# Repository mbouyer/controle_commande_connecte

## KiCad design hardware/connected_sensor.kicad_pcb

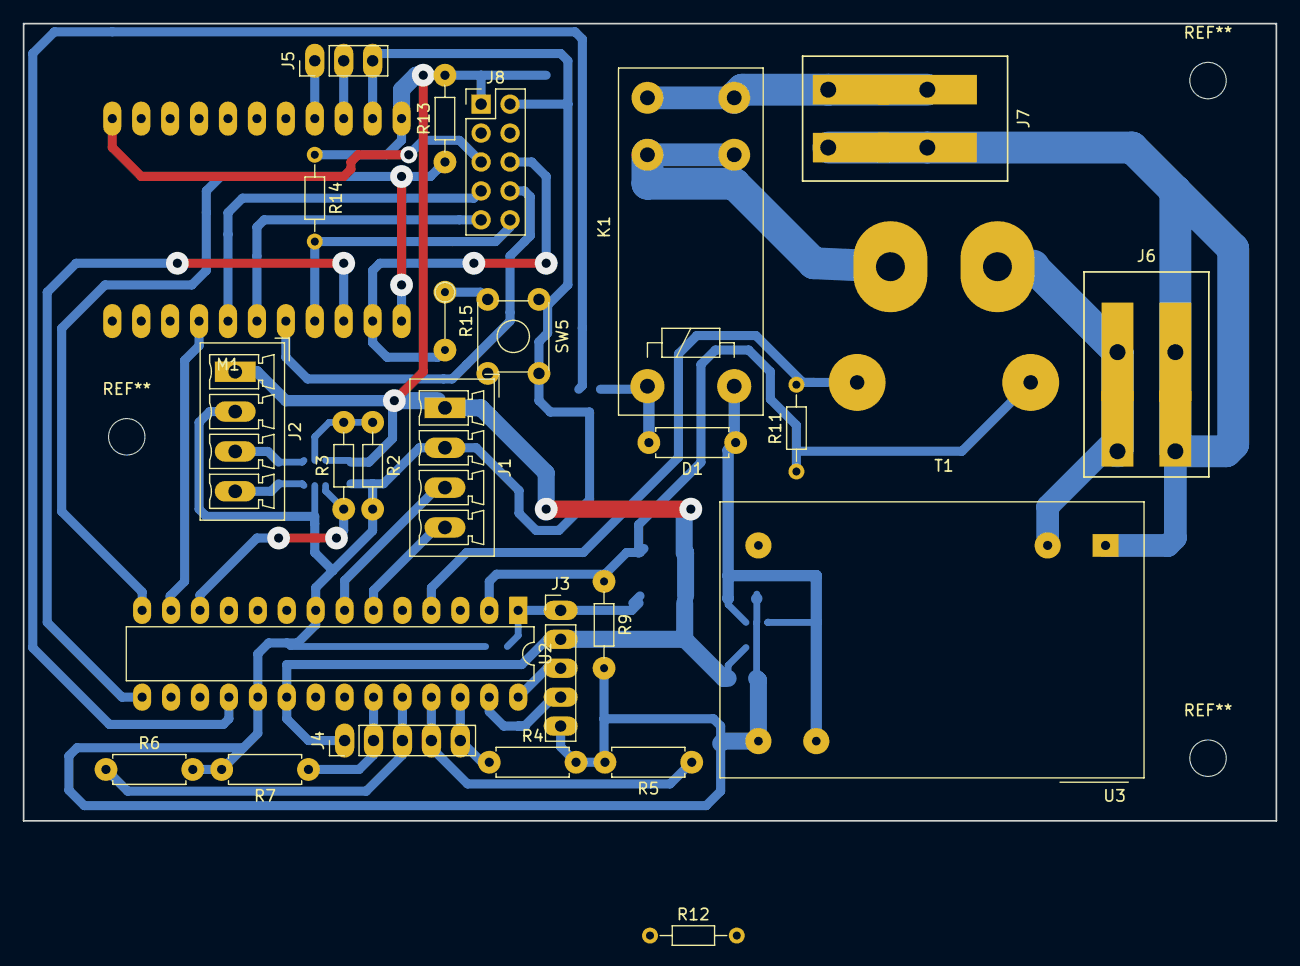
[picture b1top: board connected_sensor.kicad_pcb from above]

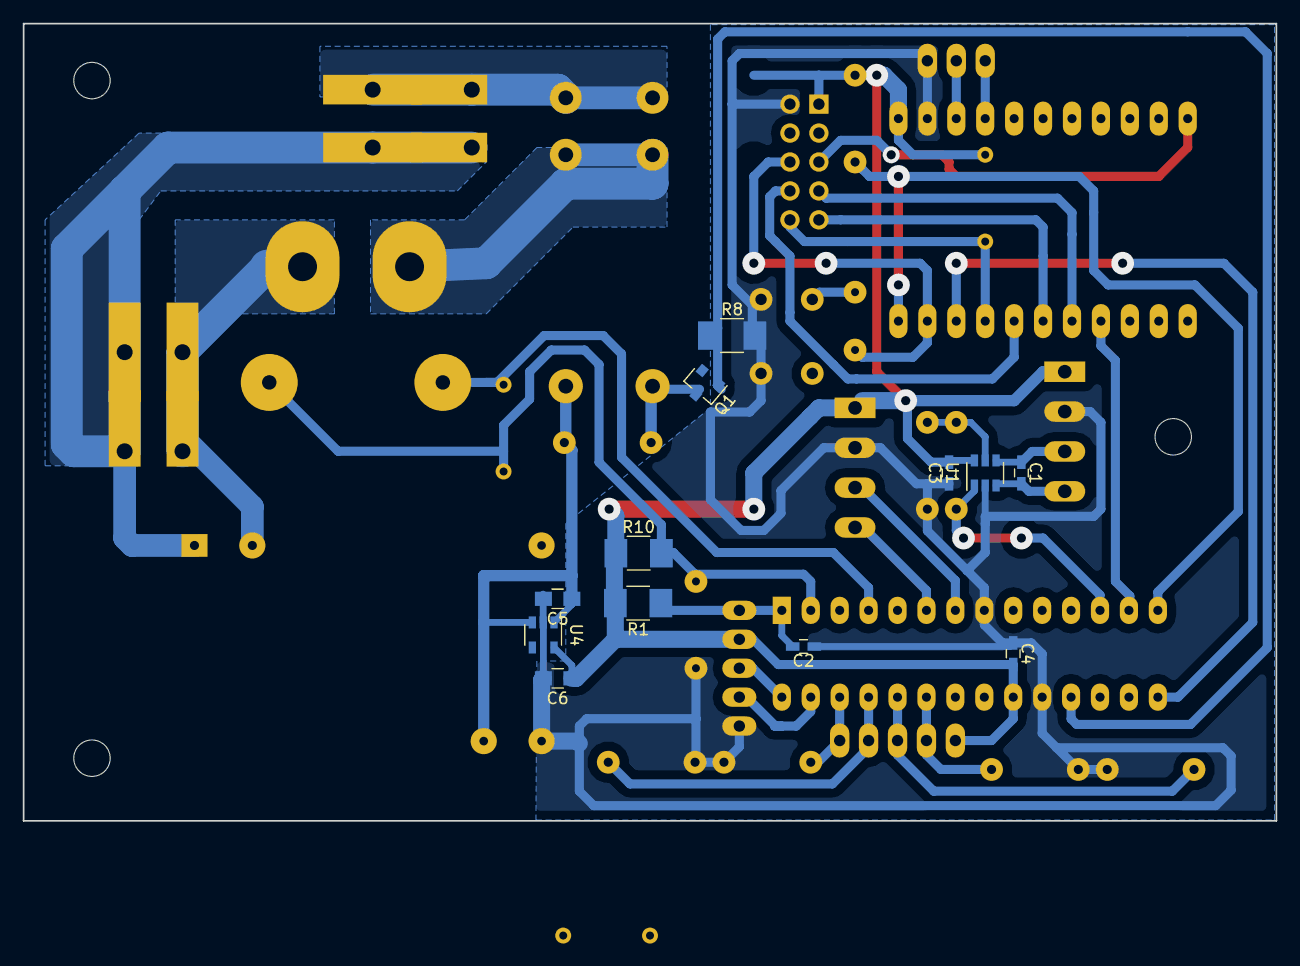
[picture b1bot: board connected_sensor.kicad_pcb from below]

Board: 2 copper layers, 110.0 x 70.0 mm, 39 parts (12 on the bottom side), 36 nets.

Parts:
C1, C2, C3, C4: 100nF; C_0603_HandSoldering
C5, C6: 1µ; C_0805_HandSoldering
D1: 1N4004; R_Axial_DIN0207_L6.3mm_D2.5mm_P7.62mm_Horizontal
J1, J2: Conn_01x04; PhoenixContact_MCV-G_04x3.50mm_Vertical
J3, J4: Conn_01x05; Pin_Header_Straight_1x05_Pitch2.54mm
J5: Conn_01x03; Pin_Header_Straight_1x03_Pitch2.54mm
J6: AC_IN; 1017491
J7: LOAD; 1017491
J8: UEXT; Pin_Header_Straight_2x05_Pitch2.54mm
K1: G2RL-1A-E 5DC; Relay_SPST_Schrack-RT1-16A-FormA_RM5mm
M1: ESP8266-DEV
Q1: ZXMN3A01FTA; SOT-23
R1, R8: 10K; R_1210_HandSoldering
R2: 5.6K; R_Axial_DIN0204_L3.6mm_D1.6mm_P7.62mm_Horizontal
R3: 100K; R_Axial_DIN0204_L3.6mm_D1.6mm_P7.62mm_Horizontal
R4, R5, R6, R7: 10K; R_Axial_DIN0207_L6.3mm_D2.5mm_P7.62mm_Horizontal
R9: 4.7k; R_Axial_DIN0204_L3.6mm_D1.6mm_P7.62mm_Horizontal
R10: 10k; R_1210_HandSoldering
R11: 18; R_Axial_DIN0204_L3.6mm_D1.6mm_P7.62mm_Horizontal
R12: NA; R_Axial_DIN0204_L3.6mm_D1.6mm_P7.62mm_Horizontal
R13: 2.2K; R_Axial_DIN0204_L3.6mm_D1.6mm_P7.62mm_Horizontal
R14: 47K; R_Axial_DIN0204_L3.6mm_D1.6mm_P7.62mm_Horizontal
R15: 220; R_Axial_DIN0204_L3.6mm_D1.6mm_P5.08mm_Vertical
SW5: SW_Push; SW_TH_Tactile_Omron_B3F-10xx
T1: Transformer_1P_1S; CSE187-LP
U1: MAX4460ESA; SOT-23-6
U2: PIC18F25Q10; DIP-28_W7.62mm_LongPads
U3: IRM-03-5; ACDC-Conv_THTMeanWell-IRM-03-XX
U4: MIC5504-3.3; SOT-23-5

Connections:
+3V3: C3.2, C4.2, C6.1, J1.1, J2.1, J3.2, J4.1, J8.1, M1.1, R1.2, R10.1, R12.2, R13.2, R14.1, U2.20, U4.5
+5V: C5.1, D1.1, K1.A2, U3.16, U4.1, U4.3
/AC1: J6.1, J7.1, U3.1
/AC2: J6.2, T1.1, U3.3
/ACL: J7.2, K1.14
/ACm: K1.11, T1.2
/BT1: J4.2, R7.1, U2.23
/BT2: J4.3, R6.1, U2.24
/BT3: J4.4, R5.1, U2.25
/BT4: J4.5, R4.1, U2.26
/CLK: J8.9, M1.17
/CS: J8.10, M1.19, R14.2
/C_D: J8.6, M1.21, R15.2
/LCD_RST: J8.5, M1.11
/MISO: J8.7, M1.16
/MOSI: J8.8, M1.18
/REL: Q1.1, R8.1, U2.18
/RXD: J5.1, M1.4
/TXD: J5.2, M1.3
CUR_REF: R9.1, R10.2, R11.1, T1.4, U2.2
CUR_SENSE: R11.2, T1.3, U2.4
DATA_READY: M1.15, U2.13
GND: C2.1, C3.1, C4.1, C5.2, C6.2, J1.2, J2.2, J3.5, J5.3, J8.2, M1.2, Q1.2, R2.2, R4.2, R5.2, R6.2, R7.2, R8.2, R9.2, SW5.1, SW5.2, U1.2, U2.8, U2.19, U3.14, U4.2
MCLR: C2.2, J3.1, R1.1, U2.1
unnamed: C1.1, J2.3, U1.6
unnamed: C1.2, J2.4, U1.3
unnamed: D1.2, K1.A1, Q1.3
unnamed: J1.3, U2.7
unnamed: J1.4, U2.6
unnamed: J3.3, U2.28
unnamed: J3.4, U2.27
unnamed: R2.1, R3.2
unnamed: R3.1, U1.1, U2.12
unnamed: R15.1, SW5.3
SCL: M1.22, R13.1, U2.14
SDA: M1.20, R12.1, U2.15

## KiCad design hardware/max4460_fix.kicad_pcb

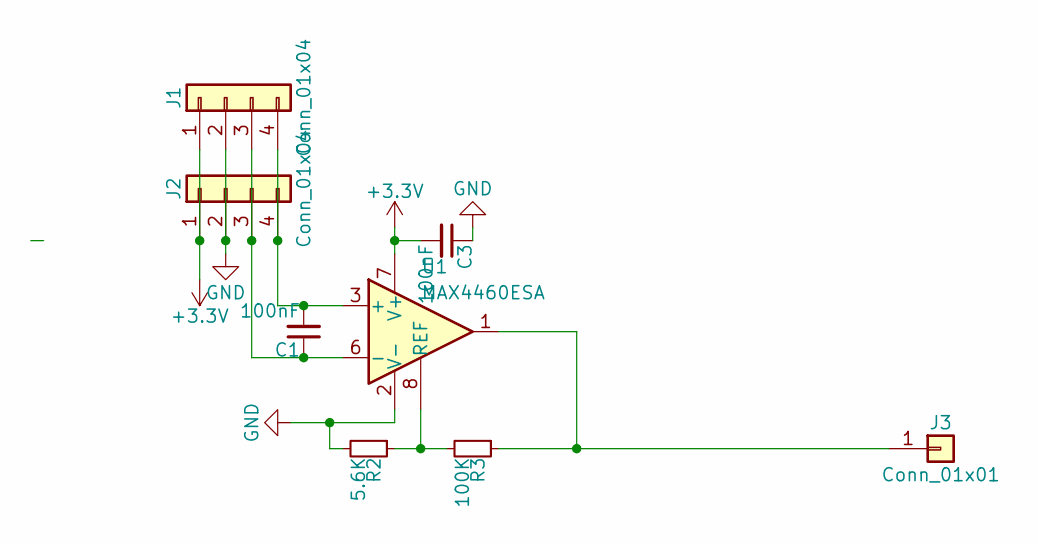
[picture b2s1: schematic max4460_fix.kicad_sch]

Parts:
C1, C3: 100nF; C_0603_HandSoldering
J1, J2: Conn_01x04; PhoenixContact_MCV-G_04x3.50mm_Vertical
J3: Conn_01x01; Pin_Header_Straight_1x01_Pitch2.54mm
R2: 5.6K; R_Axial_DIN0204_L3.6mm_D1.6mm_P7.62mm_Horizontal
R3: 100K; R_Axial_DIN0204_L3.6mm_D1.6mm_P7.62mm_Horizontal
U1: MAX4460ESA; SOIC-8_3.9x4.9mm_Pitch1.27mm

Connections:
+3V3: C3.2, J1.1, J2.1, U1.7 (V+)
GND: C3.1, J1.2, J2.2, R2.2, U1.2 (V-)
unnamed: C1.1, J1.3, J2.3, U1.6 (-)
unnamed: C1.2, J1.4, J2.4, U1.3 (+)
unnamed: J3.1, R3.1, U1.1
unnamed: R2.1, R3.2, U1.8 (REF)

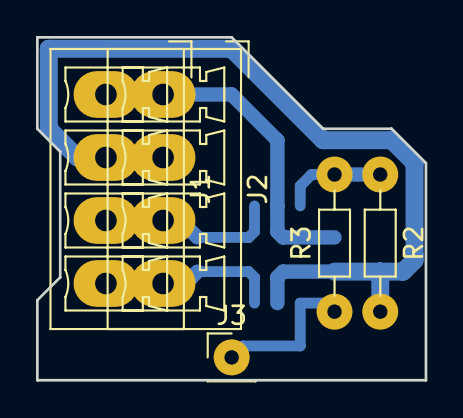
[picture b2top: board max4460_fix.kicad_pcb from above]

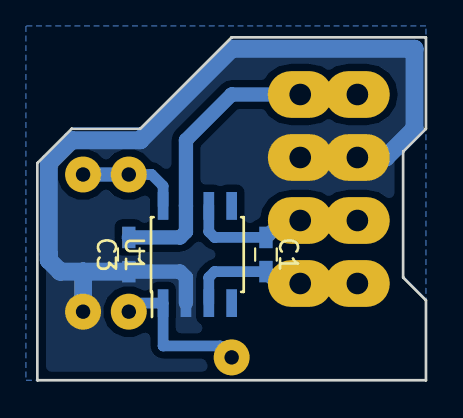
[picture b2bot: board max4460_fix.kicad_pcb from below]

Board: 2 copper layers, 21.6 x 19.0 mm, 8 parts (3 on the bottom side), 6 nets.

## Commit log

2018-12-12 Premier import, le matériel devrait être définitif
2019-01-10 max4460esa est SIOC8 et pas SOT-6; ajout d'un petit PCB d'adaptation. Il se soude sur les broches résistances et connecteur (J2) du PCB principal.
2019-02-14 Ajout des fichiers CAO pour les découpes et support écran.
2019-10-07 L'ecran necessite 2 GPIOs en plus du SPI. Re-route 2 GPIOs de l'ESP vers le connecteur ecran.
2019-10-07 Version initiale du logiciel pour les microcontrolleurs.
2019-10-17 Serve any file present in SPIFFS, with content-type based on extention. Provide sensor values as plain text. Add a wheel icon on the web page, and make it spin when the device is on. Make the css res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
2019-10-21 Forgot javascript file
2019-11-19 Add ETA and power on counter. better wifi display
2019-11-27 Ops, fix sign for ETA computaion
2019-12-18 Move wifi parameters to own include file, for privacy
2019-12-18 Implement a "NO_PIC" emulation mode, which allows testing display and some computations with a standalone esp8266 module. Fix some signed/unsigned and overflow issues with ETA
2019-12-18 Properly clear LCD also when automatically stopping motor
2022-12-01 Convert to kicad 6.x
2022-12-02 Note P/N for current transformer
2022-12-12 Add surge protections on current sensor
